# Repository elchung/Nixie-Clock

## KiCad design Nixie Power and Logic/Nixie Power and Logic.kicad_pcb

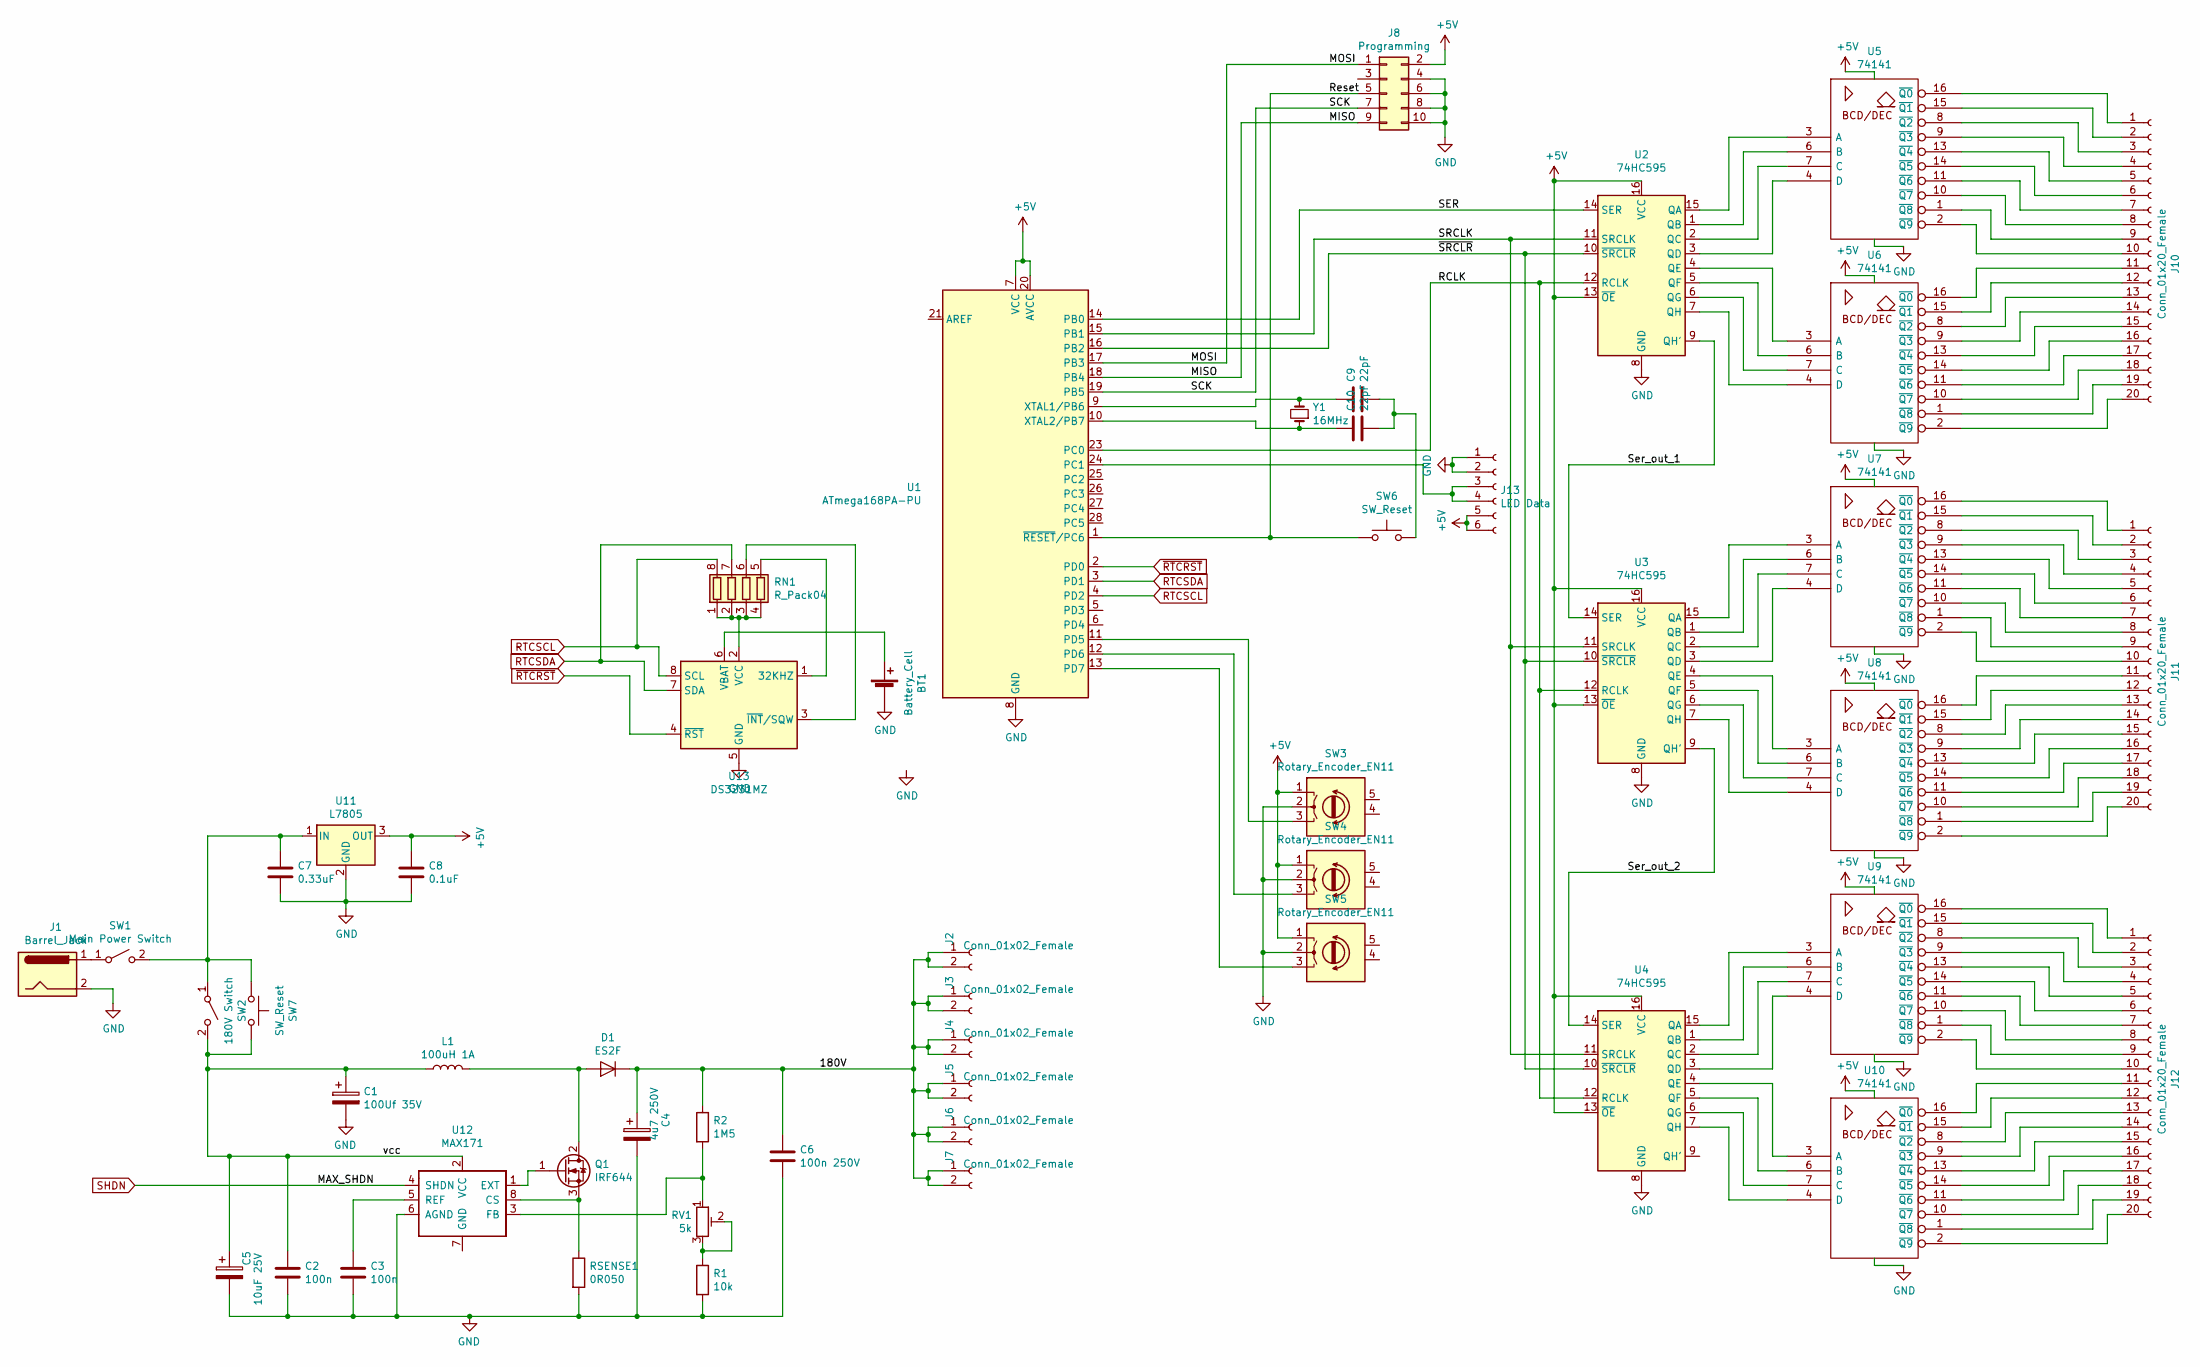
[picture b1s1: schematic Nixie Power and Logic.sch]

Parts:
BT1: Battery_Cell; BatteryHolder_Keystone_3000_1x12mm
C1: 100Uf 35V; CP_EIA-7343-31_Kemet-D_Pad2.25x2.55mm_HandSolder
C2, C3: 100n; C_0805_2012Metric_Pad1.15x1.40mm_HandSolder
C4: 4u7 250V; CP_Elec_10x14.3
C5: 10uF 25V; CP_EIA-7343-31_Kemet-D_Pad2.25x2.55mm_HandSolder
C6: 100n 250V; C_2220_5650Metric_Pad1.97x5.40mm_HandSolder
C7: 0.33uF; C_0805_2012Metric_Pad1.15x1.40mm_HandSolder
C8: 0.1uF; C_0805_2012Metric_Pad1.15x1.40mm_HandSolder
C9, C10: 22pF; C_0603_1608Metric_Pad1.05x0.95mm_HandSolder
D1: ES2F; D_SOD-214AA
J1: Barrel_Jack; BarrelJack_CUI_PJ-036AH-SMT_Horizontal
J2, J3, J4, J5, J6, J7: Conn_01x02_Female; PinHeader_1x02_P2.54mm_Vertical_SMD_Pin1Left
J8: Programming; IDC-Header_2x06_P2.54mm_Horizontal
J10, J11, J12: Conn_01x20_Female; PinHeader_1x20_P2.54mm_Vertical_SMD_Pin1Left
J13: LED Data; PinSocket_1x06_P2.54mm_Vertical_SMD_Pin1Left
L1: 100uH 1A; L_Bourns_SDR1806
Q1: IRF644; TO-220-3_Vertical
R1: 10k; R_0805_2012Metric_Pad1.15x1.40mm_HandSolder
R2: 1M5; R_2512_6332Metric_Pad1.52x3.35mm_HandSolder
RN1: R_Pack04; R_Array_Convex_4x0603
RSENSE1: 0R050; R_2010_5025Metric_Pad1.52x2.65mm_HandSolder
RV1: 5k; Potentiometer_Bourns_3214W_Vertical
SW1: Main Power Switch; SolderWirePad_1x02_P3.81mm_Drill1mm
SW2: 180V Switch; SolderWirePad_1x02_P3.81mm_Drill1mm
SW3, SW4, SW5: Rotary_Encoder_EN11; EN11-VNM Rotary Encoder
SW6: SW_Reset; SW_SPST_B3S-1000
SW7: SW_Reset; SolderWirePad_1x02_P3.81mm_Drill1mm
U1: ATmega168PA-PU; DIP-28_W7.62mm
U2, U3, U4: 74HC595; SOP65P640X110-16N
U5, U6, U7, U8, U9, U10: 74141; DIP-16_W7.62mm_Socket
U11: L7805; TO-220-3_Horizontal_TabDown
U12: MAX171; SOIC−8-NARROW
U13: DS3231MZ; SOIC-8_3.9x4.9mm_P1.27mm
Y1: 16MHz; Crystal_HC50_Vertical

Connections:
+5V: C8.1, J8.2, J13.5, J13.6, SW3.1, SW4.1, SW5.1, U1.7 (VCC), U1.20 (AVCC), U2.13 (~OE), U2.16 (VCC), U3.13 (~OE), U3.16 (VCC), U4.13 (~OE), U4.16 (VCC), U5.5 (VCC), U6.5 (VCC), U7.5 (VCC), U8.5 (VCC), U9.5 (VCC), U10.5 (VCC), U11.3 (OUT)
/180V: C4.1, C6.1, D1.1 (K), J2.1, J2.2, J3.1, J3.2, J4.1, J4.2, J5.1, J5.2, J6.1, J6.2, J7.1, J7.2, R2.1
/MISO: J8.9, U1.18 (PB4)
/MOSI: J8.1, U1.17 (PB3)
/RCLK: U1.23 (PC0), U2.12 (RCLK), U3.12 (RCLK), U4.12 (RCLK)
/Reset: J8.5, SW6.1, U1.1 (~RESET~/PC6)
/SCK: J8.7, U1.19 (PB5)
/SER: U1.14 (PB0), U2.14 (SER)
/SRCLK: U1.15 (PB1), U2.11 (SRCLK), U3.11 (SRCLK), U4.11 (SRCLK)
/Ser_out_1: U2.9 (QH'), U3.14 (SER)
/Ser_out_2: U3.9 (QH'), U4.14 (SER)
/vcc: C1.1, C2.1, C5.1, L1.2, SW2.2 (B), SW7.2, U12.2 (VCC)
/~SRCLR: U1.16 (PB2), U2.10 (~SRCLR), U3.10 (~SRCLR), U4.10 (~SRCLR)
GND: BT1.2 (-), C1.2, C2.2, C3.2, C4.2, C5.2, C6.2, C7.2, C8.2, J1.2, J8.4, J8.6, J8.8, J8.10, J13.1, J13.2, R1.2, RSENSE1.2, SW3.2, SW4.2, SW5.2, U1.8 (GND), U1.22 (GND), U2.8 (GND), U3.8 (GND), U4.8 (GND), U5.12 (GND), U6.12 (GND), U7.12 (GND), U8.12 (GND), U9.12 (GND), U10.12 (GND), U11.2 (GND), U12.6 (AGND), U13.5 (GND)
unnamed: BT1.1 (+), U13.6 (VBAT)
unnamed: C3.1, U12.5 (REF)
unnamed: C7.1, SW1.2 (B), SW2.1 (A), SW7.1, U11.1 (IN)
unnamed: C9.1, U1.9 (XTAL1/PB6), Y1.2
unnamed: C10.1, U1.10 (XTAL2/PB7), Y1.1
unnamed: C9.2, C10.2, SW6.2
unnamed: D1.2 (A), L1.1, Q1.2 (D)
unnamed: J1.1, SW1.1 (A)
unnamed: J10.1, U5.16 (~Q0)
unnamed: J10.2, U5.15 (~Q1)
unnamed: J10.3, U5.8 (~Q2)
unnamed: J10.4, U5.9 (~Q3)
unnamed: J10.5, U5.13 (~Q4)
unnamed: J10.6, U5.14 (~Q5)
unnamed: J10.7, U5.11 (~Q6)
unnamed: J10.8, U5.10 (~Q7)
unnamed: J10.9, U5.1 (~Q8)
unnamed: J10.10, U5.2 (~Q9)
unnamed: J10.11, U6.16 (~Q0)
unnamed: J10.12, U6.15 (~Q1)
unnamed: J10.13, U6.8 (~Q2)
unnamed: J10.14, U6.9 (~Q3)
unnamed: J10.15, U6.13 (~Q4)
unnamed: J10.16, U6.14 (~Q5)
unnamed: J10.17, U6.11 (~Q6)
unnamed: J10.18, U6.10 (~Q7)
unnamed: J10.19, U6.1 (~Q8)
unnamed: J10.20, U6.2 (~Q9)
unnamed: J11.1, U7.16 (~Q0)
unnamed: J11.2, U7.15 (~Q1)
unnamed: J11.3, U7.8 (~Q2)
unnamed: J11.4, U7.9 (~Q3)
unnamed: J11.5, U7.13 (~Q4)
unnamed: J11.6, U7.14 (~Q5)
unnamed: J11.7, U7.11 (~Q6)
unnamed: J11.8, U7.10 (~Q7)
unnamed: J11.9, U7.1 (~Q8)
unnamed: J11.10, U7.2 (~Q9)
unnamed: J11.11, U8.16 (~Q0)
unnamed: J11.12, U8.15 (~Q1)
unnamed: J11.13, U8.8 (~Q2)
unnamed: J11.14, U8.9 (~Q3)
unnamed: J11.15, U8.13 (~Q4)
unnamed: J11.16, U8.14 (~Q5)
unnamed: J11.17, U8.11 (~Q6)
unnamed: J11.18, U8.10 (~Q7)
unnamed: J11.19, U8.1 (~Q8)
unnamed: J11.20, U8.2 (~Q9)
unnamed: J12.1, U9.16 (~Q0)
unnamed: J12.2, U9.15 (~Q1)
unnamed: J12.3, U9.8 (~Q2)
unnamed: J12.4, U9.9 (~Q3)
unnamed: J12.5, U9.13 (~Q4)
unnamed: J12.6, U9.14 (~Q5)
unnamed: J12.7, U9.11 (~Q6)
unnamed: J12.8, U9.10 (~Q7)
unnamed: J12.9, U9.1 (~Q8)
unnamed: J12.10, U9.2 (~Q9)
unnamed: J12.11, U10.16 (~Q0)
unnamed: J12.12, U10.15 (~Q1)
unnamed: J12.13, U10.8 (~Q2)
unnamed: J12.14, U10.9 (~Q3)
unnamed: J12.15, U10.13 (~Q4)
unnamed: J12.16, U10.14 (~Q5)
unnamed: J12.17, U10.11 (~Q6)
unnamed: J12.18, U10.10 (~Q7)
unnamed: J12.19, U10.1 (~Q8)
unnamed: J12.20, U10.2 (~Q9)
unnamed: J13.3, J13.4, U1.24 (PC1)
unnamed: Q1.1 (G), U12.1 (EXT)
unnamed: Q1.3 (S), RSENSE1.1, U12.8 (CS)
unnamed: R1.1, RV1.2, RV1.3
unnamed: R2.2, RV1.1, U12.3 (FB)
unnamed: RN1.1 (R1.1), RN1.2 (R2.1), RN1.3 (R3.1), RN1.4 (R4.1), U13.2 (VCC)
unnamed: RN1.5 (R4.2), U13.1 (32KHZ)
unnamed: RN1.6 (R3.2), U13.3 (~INT~/SQW)
unnamed: SW3.3, U1.11 (PD5)
unnamed: SW4.3, U1.12 (PD6)
unnamed: SW5.3, U1.13 (PD7)
unnamed: U2.1 (QB), U5.6 (B)
unnamed: U2.2 (QC), U5.7 (C)
unnamed: U2.3 (QD), U5.4 (D)
unnamed: U2.4 (QE), U6.3 (A)
unnamed: U2.5 (QF), U6.6 (B)
unnamed: U2.6 (QG), U6.7 (C)
unnamed: U2.7 (QH), U6.4 (D)
unnamed: U2.15 (QA), U5.3 (A)
unnamed: U3.1 (QB), U7.6 (B)
unnamed: U3.2 (QC), U7.7 (C)
unnamed: U3.3 (QD), U7.4 (D)
unnamed: U3.4 (QE), U8.3 (A)
unnamed: U3.5 (QF), U8.6 (B)
unnamed: U3.6 (QG), U8.7 (C)
unnamed: U3.7 (QH), U8.4 (D)
unnamed: U3.15 (QA), U7.3 (A)
unnamed: U4.1 (QB), U9.6 (B)
unnamed: U4.2 (QC), U9.7 (C)
unnamed: U4.3 (QD), U9.4 (D)
unnamed: U4.15 (QA), U9.3 (A)
unnamed: U4.4 (QE), U10.3 (A)
unnamed: U4.7 (QH), U10.4 (D)
unnamed: U4.5 (QF), U10.6 (B)
unnamed: U4.6 (QG), U10.7 (C)
RTCSCL: RN1.8 (R1.2), U1.4 (PD2), U13.8 (SCL)
RTCSDA: RN1.7 (R2.2), U1.3 (PD1), U13.7 (SDA)
SHDN: U12.4 (SHDN)
~RTCRST: U1.2 (PD0), U13.4 (~RST)

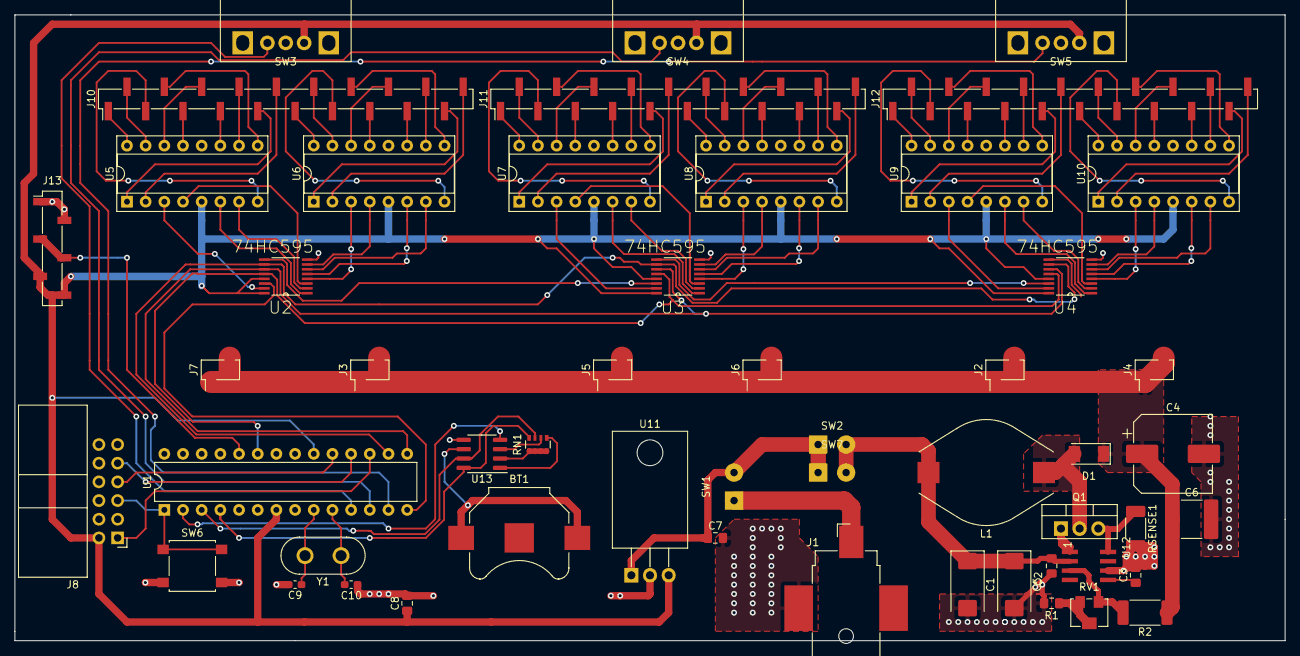
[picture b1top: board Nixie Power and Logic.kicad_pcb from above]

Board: 2 copper layers, 172.7 x 85.1 mm, 52 parts (0 on the bottom side), 120 nets.

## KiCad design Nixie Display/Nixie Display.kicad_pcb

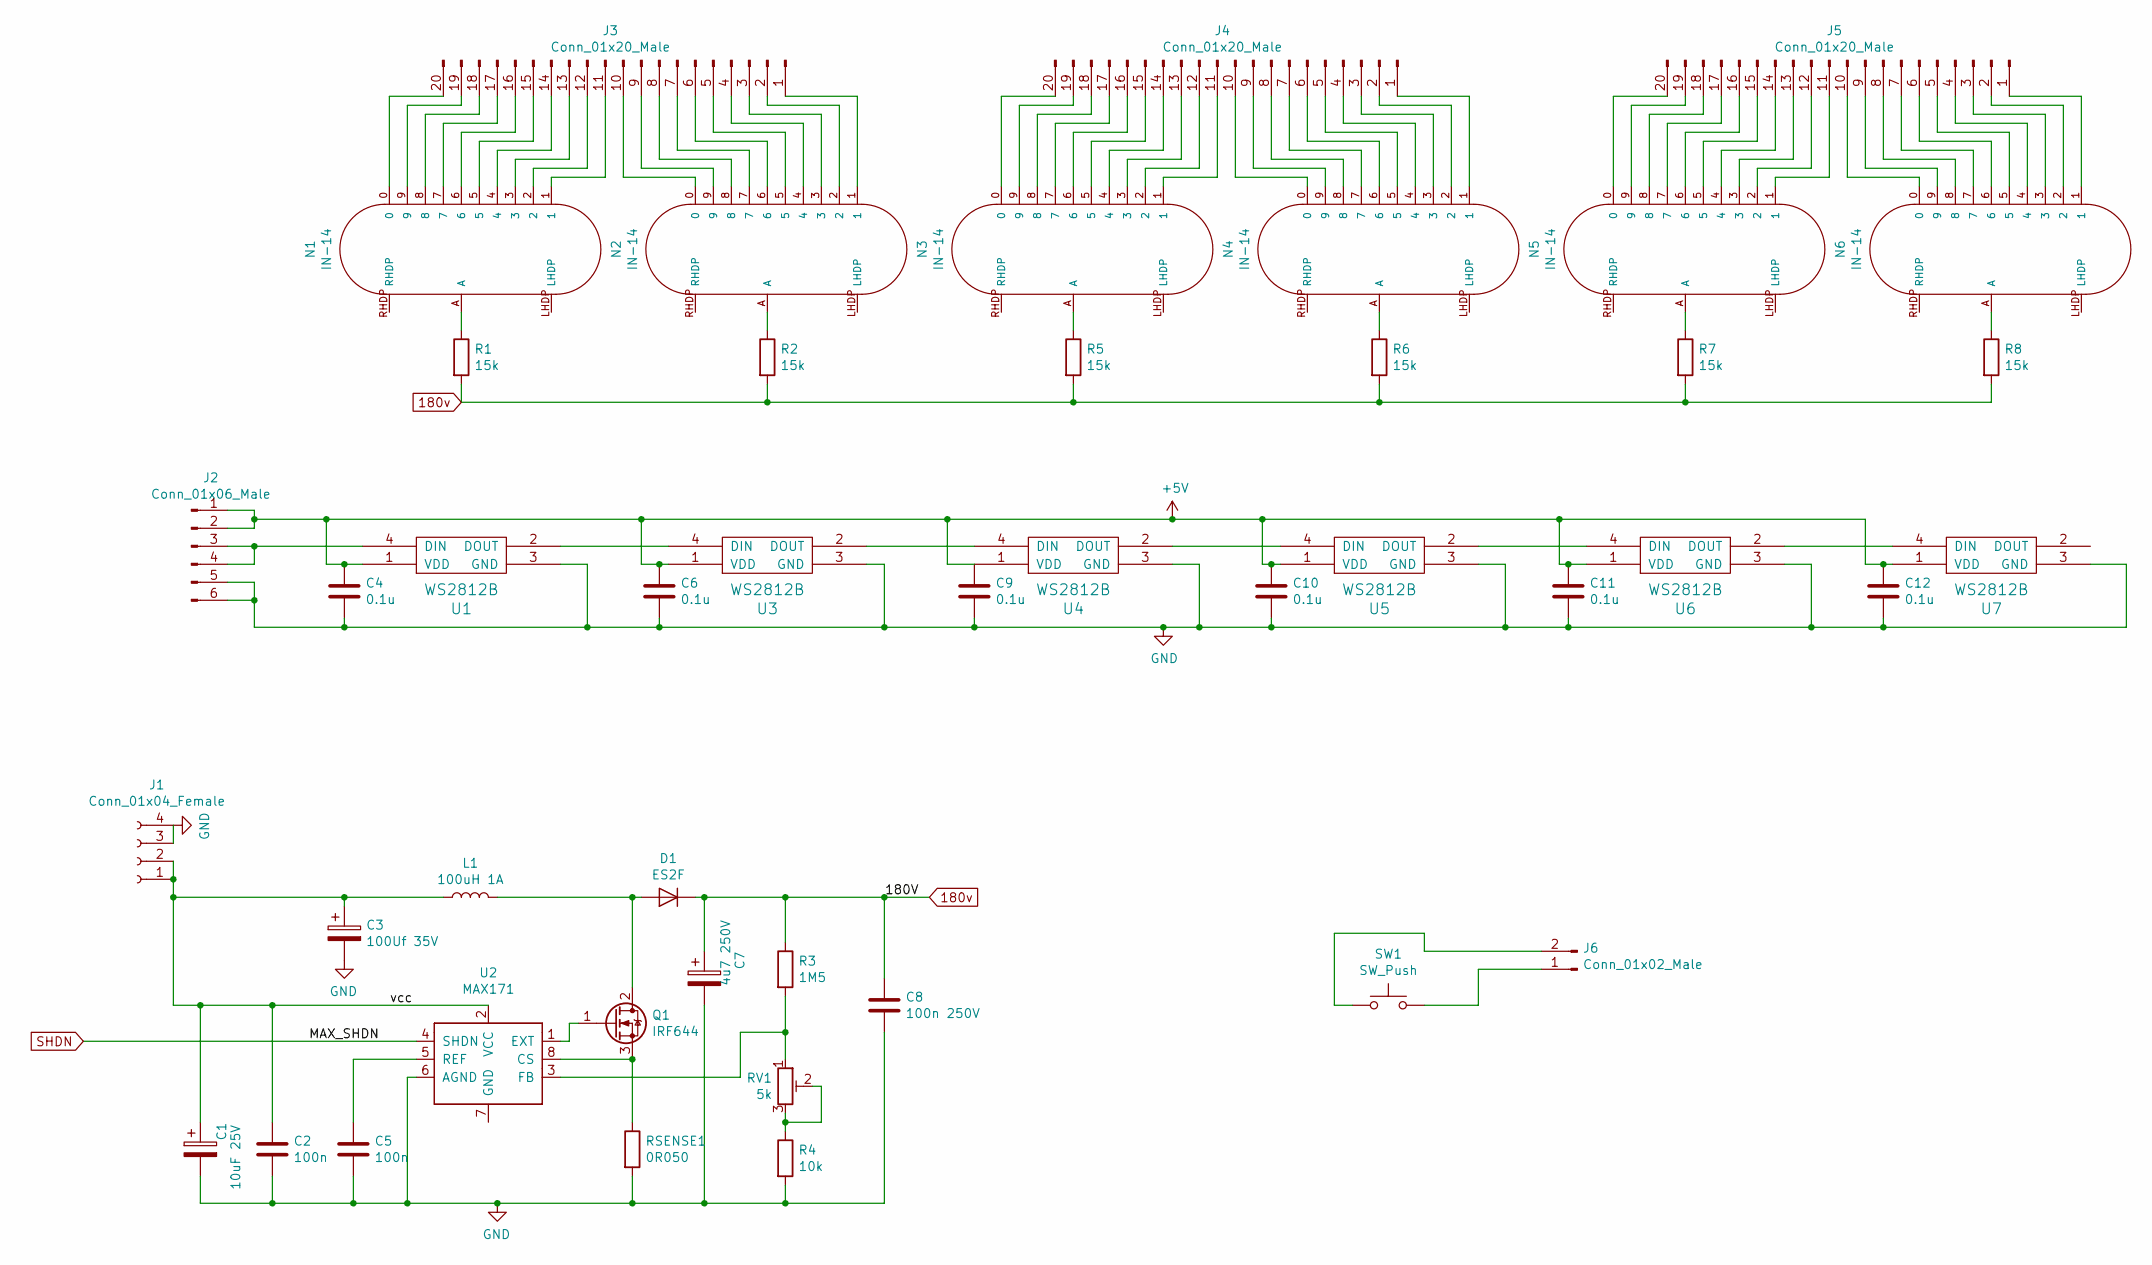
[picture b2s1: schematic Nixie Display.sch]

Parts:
C1: 10uF 25V; CP_EIA-7343-31_Kemet-D_Pad2.25x2.55mm_HandSolder
C2, C5: 100n; C_0805_2012Metric_Pad1.15x1.40mm_HandSolder
C3: 100Uf 35V; CP_EIA-7343-31_Kemet-D_Pad2.25x2.55mm_HandSolder
C4, C6, C9, C10, C11, C12: 0.1u; C_0603_1608Metric_Pad1.05x0.95mm_HandSolder
C7: 4u7 250V; CP_Elec_10x14.3
C8: 100n 250V; C_2220_5650Metric_Pad1.97x5.40mm_HandSolder
D1: ES2F; D_SOD-214AA
J1: Conn_01x04_Female; PinHeader_1x04_P2.54mm_Vertical_SMD_Pin1Left
J2: Conn_01x06_Male; PinHeader_1x06_P2.54mm_Vertical
J3, J4, J5: Conn_01x20_Male; PinHeader_1x20_P2.54mm_Vertical_SMD_Pin1Left
J6: Conn_01x02_Male; PinHeader_1x02_P2.54mm_Vertical_SMD_Pin1Left
L1: 100uH 1A; L_Bourns_SDR1806
N1, N2, N3, N4, N5, N6: IN-14; russian-nixies-IN-14
Q1: IRF644; TO-220-3_Vertical
R1, R2, R5, R6, R7, R8: 15k; R_0603_1608Metric_Pad1.05x0.95mm_HandSolder
R3: 1M5; R_2512_6332Metric_Pad1.52x3.35mm_HandSolder
R4: 10k; R_0805_2012Metric_Pad1.15x1.40mm_HandSolder
RSENSE1: 0R050; R_2010_5025Metric_Pad1.52x2.65mm_HandSolder
RV1: 5k; Potentiometer_Bourns_3214W_Vertical
SW1: SW_Push; SW_SPST_B3S-1000
U1, U3, U4, U5, U6, U7: WS2812B; LED_WS2812B_PLCC4_5.0x5.0mm_P3.2mm
U2: MAX171; SOIC−8-NARROW

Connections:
180v: C7.1, C8.1, D1.1 (K), R1.2, R2.2, R3.1, R5.2, R6.2, R7.2, R8.2
+5V: C4.1, C6.1, C9.1, C10.1, C11.1, C12.1, J2.1, J2.2, U1.1 (VDD), U3.1 (VDD), U4.1 (VDD), U5.1 (VDD), U6.1 (VDD), U7.1 (VDD)
/vcc: C1.1, C2.1, C3.1, J1.1, J1.2, L1.2, U2.2 (VCC)
GND: C1.2, C2.2, C3.2, C4.2, C5.2, C6.2, C7.2, C8.2, C9.2, C10.2, C11.2, C12.2, J1.3, J1.4, J2.5, J2.6, R4.2, RSENSE1.2, U1.3 (GND), U2.6 (AGND), U3.3 (GND), U4.3 (GND), U5.3 (GND), U6.3 (GND), U7.3 (GND)
unnamed: C5.1, U2.5 (REF)
unnamed: D1.2 (A), L1.1, Q1.2 (D)
unnamed: J2.3, J2.4, U1.4 (DIN)
unnamed: J3.1, N2.1
unnamed: J3.2, N2.2
unnamed: J3.3, N2.3
unnamed: J3.4, N2.4
unnamed: J3.5, N2.5
unnamed: J3.6, N2.6
unnamed: J3.7, N2.7
unnamed: J3.8, N2.8
unnamed: J3.9, N2.9
unnamed: J3.10, N2.0
unnamed: J3.11, N1.1
unnamed: J3.12, N1.2
unnamed: J3.13, N1.3
unnamed: J3.14, N1.4
unnamed: J3.15, N1.5
unnamed: J3.16, N1.6
unnamed: J3.17, N1.7
unnamed: J3.18, N1.8
unnamed: J3.19, N1.9
unnamed: J3.20, N1.0
unnamed: J4.1, N4.1
unnamed: J4.2, N4.2
unnamed: J4.3, N4.3
unnamed: J4.4, N4.4
unnamed: J4.5, N4.5
unnamed: J4.6, N4.6
unnamed: J4.7, N4.7
unnamed: J4.8, N4.8
unnamed: J4.9, N4.9
unnamed: J4.10, N4.0
unnamed: J4.11, N3.1
unnamed: J4.12, N3.2
unnamed: J4.13, N3.3
unnamed: J4.14, N3.4
unnamed: J4.15, N3.5
unnamed: J4.16, N3.6
unnamed: J4.17, N3.7
unnamed: J4.18, N3.8
unnamed: J4.19, N3.9
unnamed: J4.20, N3.0
unnamed: J5.1, N6.1
unnamed: J5.2, N6.2
unnamed: J5.3, N6.3
unnamed: J5.4, N6.4
unnamed: J5.5, N6.5
unnamed: J5.6, N6.6
unnamed: J5.7, N6.7
unnamed: J5.8, N6.8
unnamed: J5.9, N6.9
unnamed: J5.10, N6.0
unnamed: J5.11, N5.1
unnamed: J5.12, N5.2
unnamed: J5.13, N5.3
unnamed: J5.14, N5.4
unnamed: J5.15, N5.5
unnamed: J5.16, N5.6
unnamed: J5.17, N5.7
unnamed: J5.18, N5.8
unnamed: J5.19, N5.9
unnamed: J5.20, N5.0
unnamed: J6.1, SW1.2
unnamed: J6.2, SW1.1
unnamed: N1.A, R1.1
unnamed: N2.A, R2.1
unnamed: N3.A, R5.1
unnamed: N4.A, R6.1
unnamed: N5.A, R7.1
unnamed: N6.A, R8.1
unnamed: Q1.1 (G), U2.1 (EXT)
unnamed: Q1.3 (S), RSENSE1.1, U2.8 (CS)
unnamed: R3.2, RV1.1, U2.3 (FB)
unnamed: R4.1, RV1.2, RV1.3
unnamed: U1.2 (DOUT), U3.4 (DIN)
unnamed: U3.2 (DOUT), U4.4 (DIN)
unnamed: U4.2 (DOUT), U5.4 (DIN)
unnamed: U5.2 (DOUT), U6.4 (DIN)
unnamed: U6.2 (DOUT), U7.4 (DIN)
SHDN: U2.4 (SHDN)

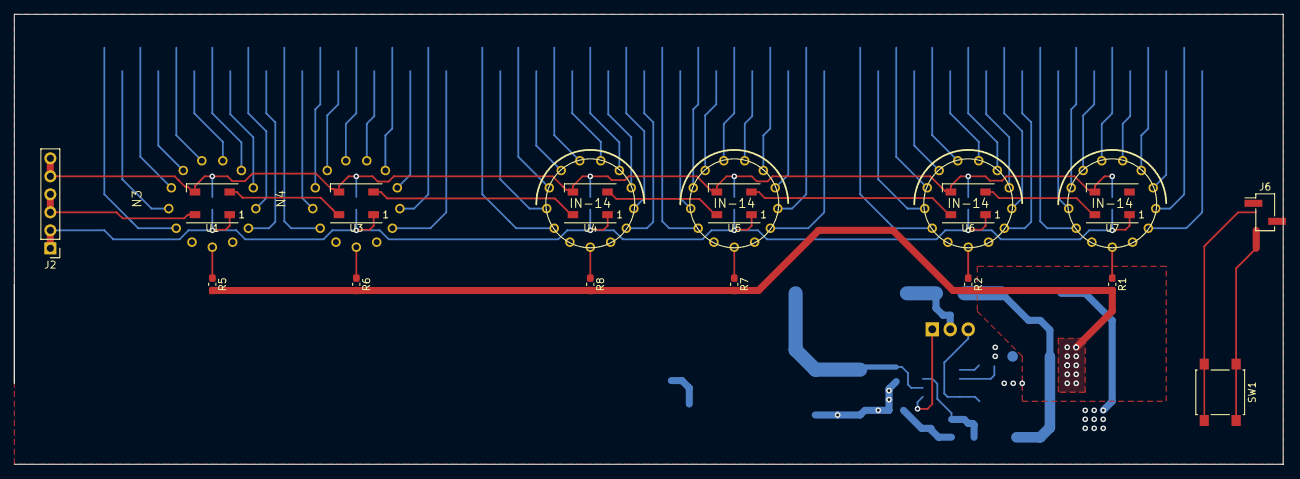
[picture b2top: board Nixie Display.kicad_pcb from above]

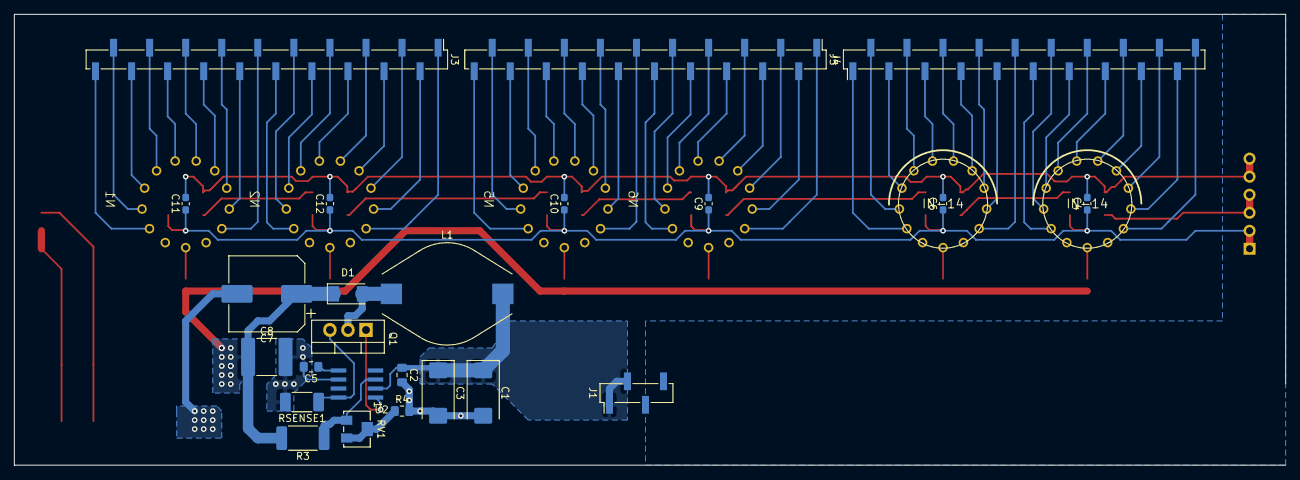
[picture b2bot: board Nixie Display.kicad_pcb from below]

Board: 2 copper layers, 179.1 x 63.5 mm, 45 parts (26 on the bottom side), 84 nets.

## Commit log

2019-09-17 Initial commit of project files
2019-10-01 Final V1.0 design. Different sized boards for top and bottom layer. Goal for v2.0 is to have matching top and bottom pcbas
